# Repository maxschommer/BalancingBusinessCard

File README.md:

# business card

This is a persistence-of-vision (POV) business card, which is also NFC enabled
to aid in sharing contact information. POV is enabled by an accelerometer which
detects the end points of a swing of the card made by the user, and arranges
the letters to flash at the correct time in between two estimated end points
(the future end-point is guessed at by the length of the previous swing). Settings are changed by a capacitive sense button.

# Directory Structure

The firmare of the card is located in the `src` directory. The electrical
design files are in `design/business_card`. Images and other media are inside
`media`.

- [src](src/)
  - Contains the firmware of the card
- [design](design/)
  - Contains the KiCAD design files of the board
- [card_manufacturing](card_manufacturing/)
  - Contains python scripts used to generate GCODE to laser etch the aluminum top of the card.
- [media](media/)
  - Contains media (gifs, images, etc.)

# Building and Flashing Firmware

In order to flash the firmware, you must have the AVR toolchain installed.

`sudo apt-get install binutils gcc-avr avr-libc uisp avrdude flex byacc bison`

Then, navigate to the `src` directory and run `make` to build the object
file. In order to flash a business card, make sure to have your AVR programmer
plugged into your computer and connected to the board (and make sure the board
is appropriately powered!), then run

`make flash`

avrdude should say the the flash was successfull.

# Running manufacturing scripts

Some helper scripts exist to automate a lot of the manufacturing process for
customization. The scripts are specific to GRBL capable CNC machines (which
can laser etch). Scripts are written in python, and can be installed by
downloading the repository and running:

`pip install -e .`

Once the dependencies are installed, the scripts can be run from the root
directory, for example:

`python -m card_manufacturing.gcode_streamer`

## image_to_laser

This is a command line argument script which converts an image to an efficiently
rastered laser etcher GCODE path. It makes sure to utilize [laser mode](https://github.com/gnea/grbl/wiki/Grbl-v1.1-Laser-Mode) which
has been implemented in GRBL v1.1. The image is thresholded and the laser path
is binary (since the etching is all or nothing on coated aluminum). To get the
help for the script run:

`python -m card_manufacturing.image_to_laser -h`

## laser_calibration

This script generates a GCODE path to calibrate a CNC (with Z travel) with a
laser attachment. It progressively creates lines at different Z levels and
marks what the Z difference was on the line, so the user can identify the line
with the best marking and apply the appropriate offset for future etches. To
get the help for the script run:

`python -m card_manufacturing.laser_calibration -h`

## gcode_streamer

Finally, once GCODE is generated, the following script will stream the GCODE
to the CNC to run the part. To get the help for the script run:

`python -m card_manufacturing.gcode_streamer -h`

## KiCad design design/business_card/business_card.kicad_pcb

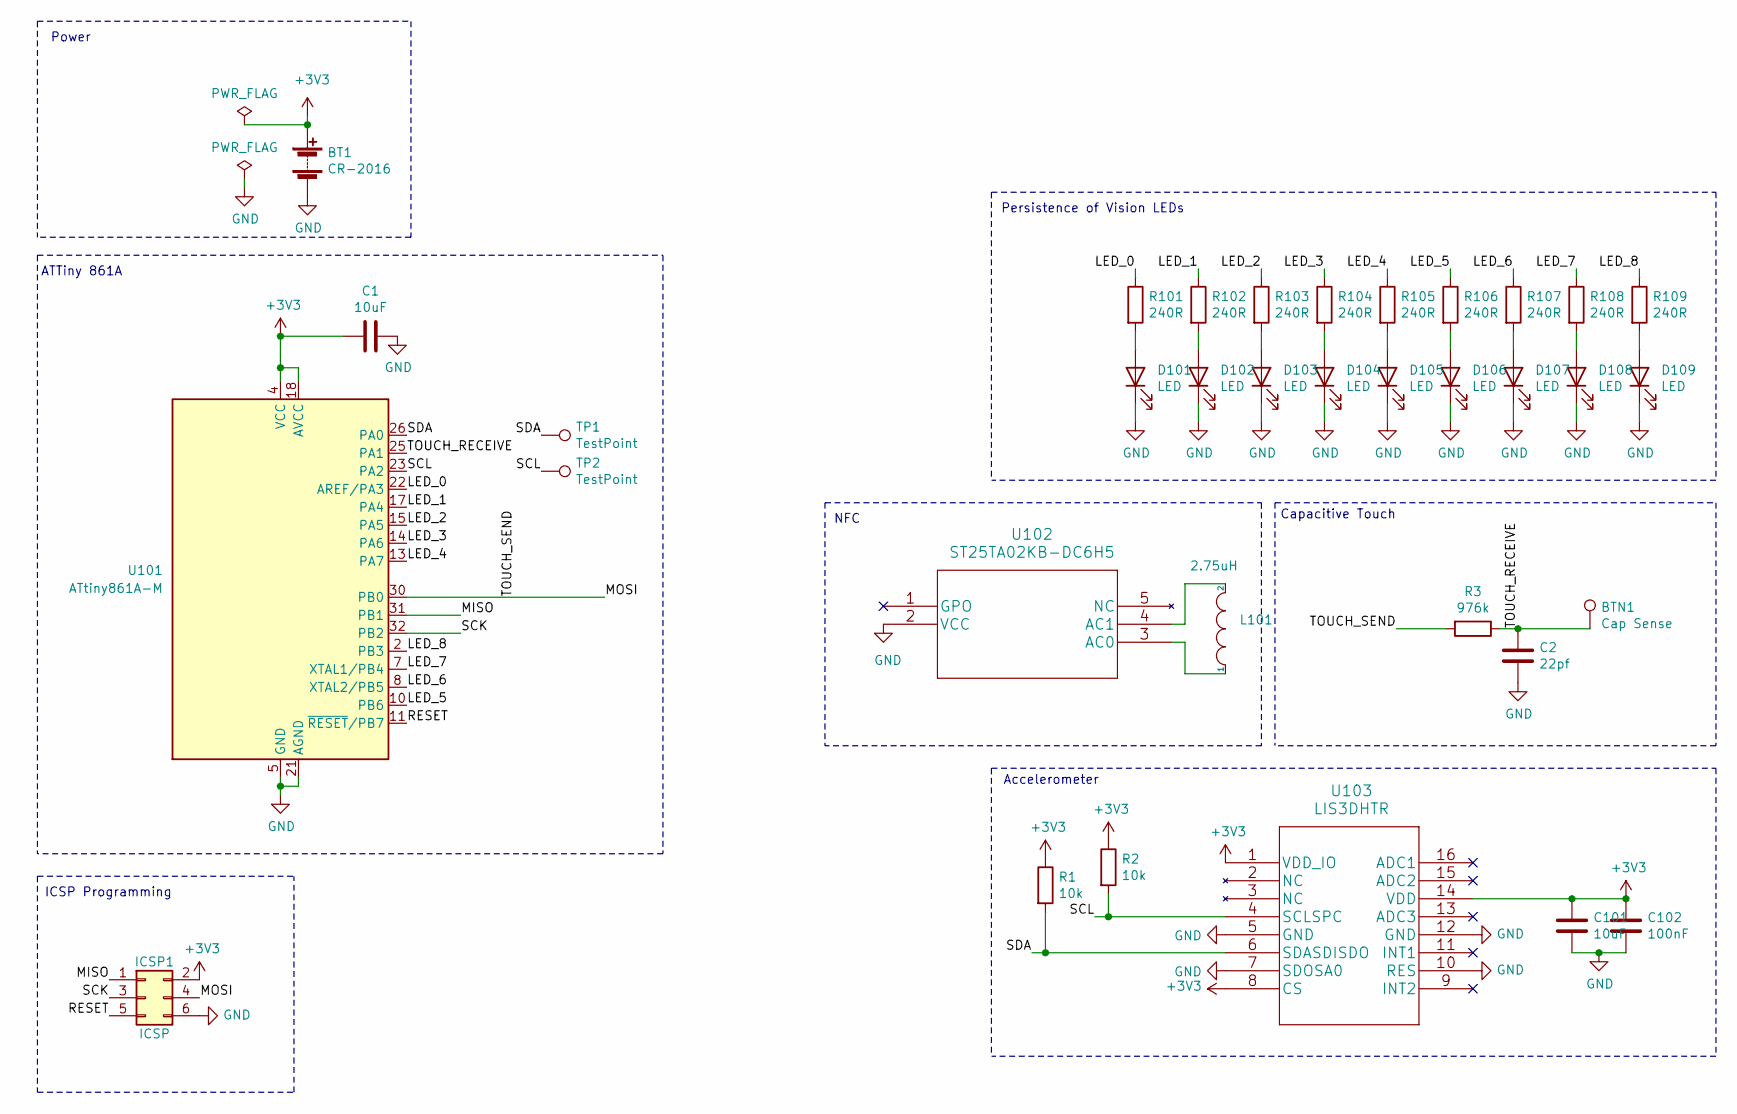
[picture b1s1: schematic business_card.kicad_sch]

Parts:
BT1: CR-2016; CR2016VP
BTN1: Cap Sense; CAP_TOUCH
C1, C101: 10uF; C_0805_2012Metric; Digikey 1276-6456-1-ND
C2: 22pf; C_0603_1608Metric; Digikey 732-7762-1-ND
C102: 100nF; C_0603_1608Metric; Digikey 311-1779-1-ND
D101, D102, D103, D104, D105, D106, D107, D108, D109: LED; LED_0603_1608Metric; Digikey 160-1183-1-ND
ICSP1: ICSP; PinHeader_2x03_P2.54mm_Vertical
L101: 2.75uH; Trace_Inductor_2_75uH
R1, R2: 10k; R_0603_1608Metric; Digikey 311-10KGRCT-ND
R3: 976k; R_0603_1608Metric; Digikey 311-976KHRCT-ND
R101, R102, R103, R104, R105, R106, R107, R108, R109: 240R; R_0603_1608Metric; Digikey 311-240GRCT-ND
TP1, TP2: TestPoint; TestPoint_Pad_D1.0mm
U101: ATtiny861A-M; QFN-32-1EP_5x5mm_P0.5mm_EP3.1x3.1mm; Digikey ATTINY861-15MZCT-ND
U102: ST25TA02KB-DC6H5; Digikey 497-19639-1-ND
U103: LIS3DHTR; Digikey 497-10613-1-ND

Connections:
+3V3: BT1.1 (+), C1.1, C101.1, C102.1, ICSP1.2, R1.1, R2.1, U101.4 (VCC), U101.18 (AVCC), U103.1 (VDD_IO), U103.8 (CS), U103.14 (VDD)
/LED_0: R101.1, U101.22 (AREF/PA3)
/LED_1: R102.1, U101.17 (PA4)
/LED_2: R103.1, U101.15 (PA5)
/LED_3: R104.1, U101.14 (PA6)
/LED_4: R105.1, U101.13 (PA7)
/LED_5: R106.1, U101.10 (PB6)
/LED_6: R107.1, U101.8 (XTAL2/PB5)
/LED_7: R108.1, U101.7 (XTAL1/PB4)
/LED_8: R109.1, U101.2 (PB3)
/MISO: ICSP1.1, U101.31 (PB1)
/MOSI: ICSP1.4, R3.2, U101.30 (PB0)
/RESET: ICSP1.5, U101.11 (~RESET~/PB7)
/SCK: ICSP1.3, U101.32 (PB2)
/SCL: R2.2, TP2.1, U101.23 (PA2), U103.4 (SCLSPC)
/SDA: R1.2, TP1.1, U101.26 (PA0), U103.6 (SDASDISDO)
/TOUCH_RECEIVE: BTN1.1, C2.1, R3.1, U101.25 (PA1)
GND: BT1.2 (-), C1.2, C2.2, C101.2, C102.2, D101.1 (K), D102.1 (K), D103.1 (K), D104.1 (K), D105.1 (K), D106.1 (K), D107.1 (K), D108.1 (K), D109.1 (K), ICSP1.6, U101.5 (GND), U101.21 (AGND), U101.33 (GND), U102.2 (VCC), U103.5 (GND), U103.7 (SDOSA0), U103.10 (RES), U103.12 (GND)
unnamed: D101.2 (A), R101.2
unnamed: D102.2 (A), R102.2
unnamed: D103.2 (A), R103.2
unnamed: D104.2 (A), R104.2
unnamed: D105.2 (A), R105.2
unnamed: D106.2 (A), R106.2
unnamed: D107.2 (A), R107.2
unnamed: D108.2 (A), R108.2
unnamed: D109.2 (A), R109.2
unnamed: L101.1, U102.3 (AC0)
unnamed: L101.2, U102.4 (AC1)

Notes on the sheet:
Power
ATTiny 861A
ICSP Programming
NFC
Accelerometer
Persistence of Vision LEDs
Capacitive Touch

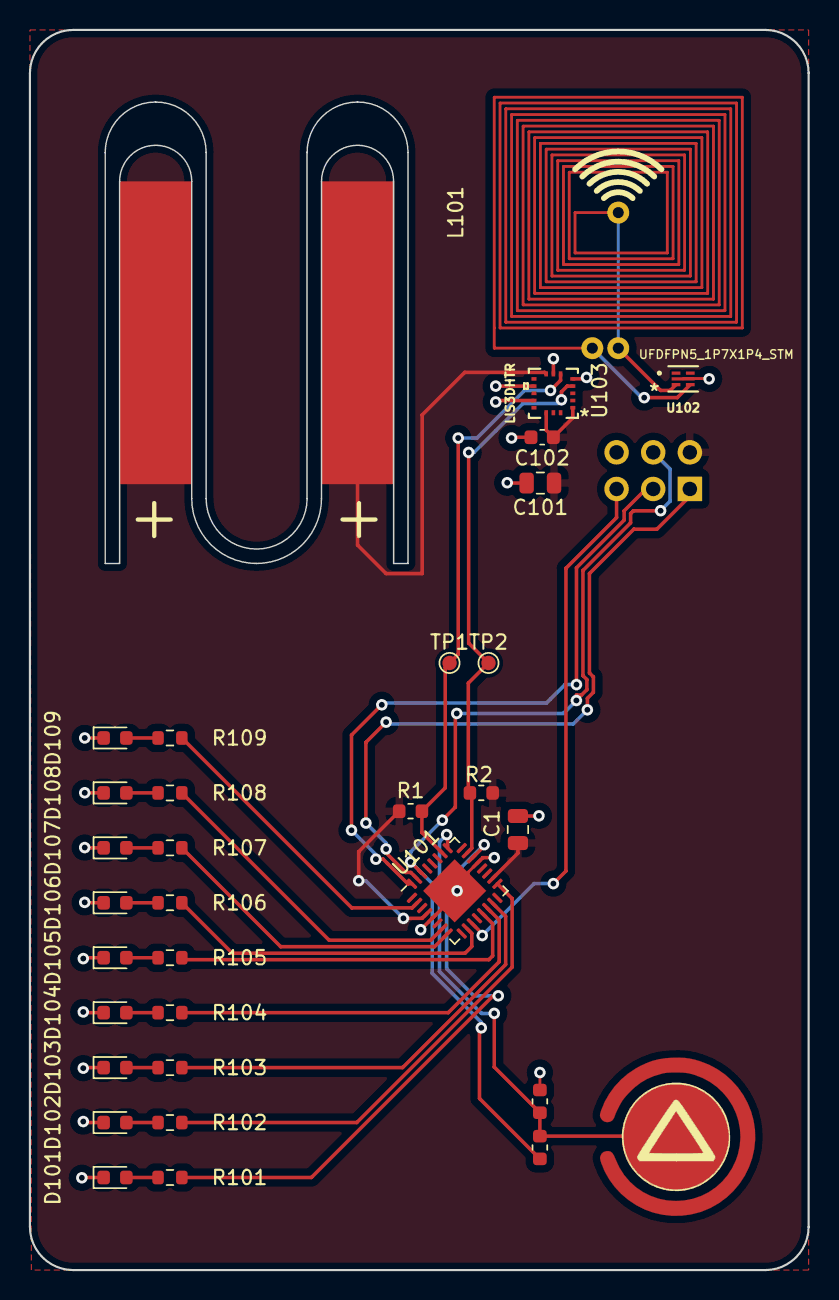
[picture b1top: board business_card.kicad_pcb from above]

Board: 2 copper layers, 54.0 x 86.0 mm, 34 parts (1 on the bottom side), 29 nets.

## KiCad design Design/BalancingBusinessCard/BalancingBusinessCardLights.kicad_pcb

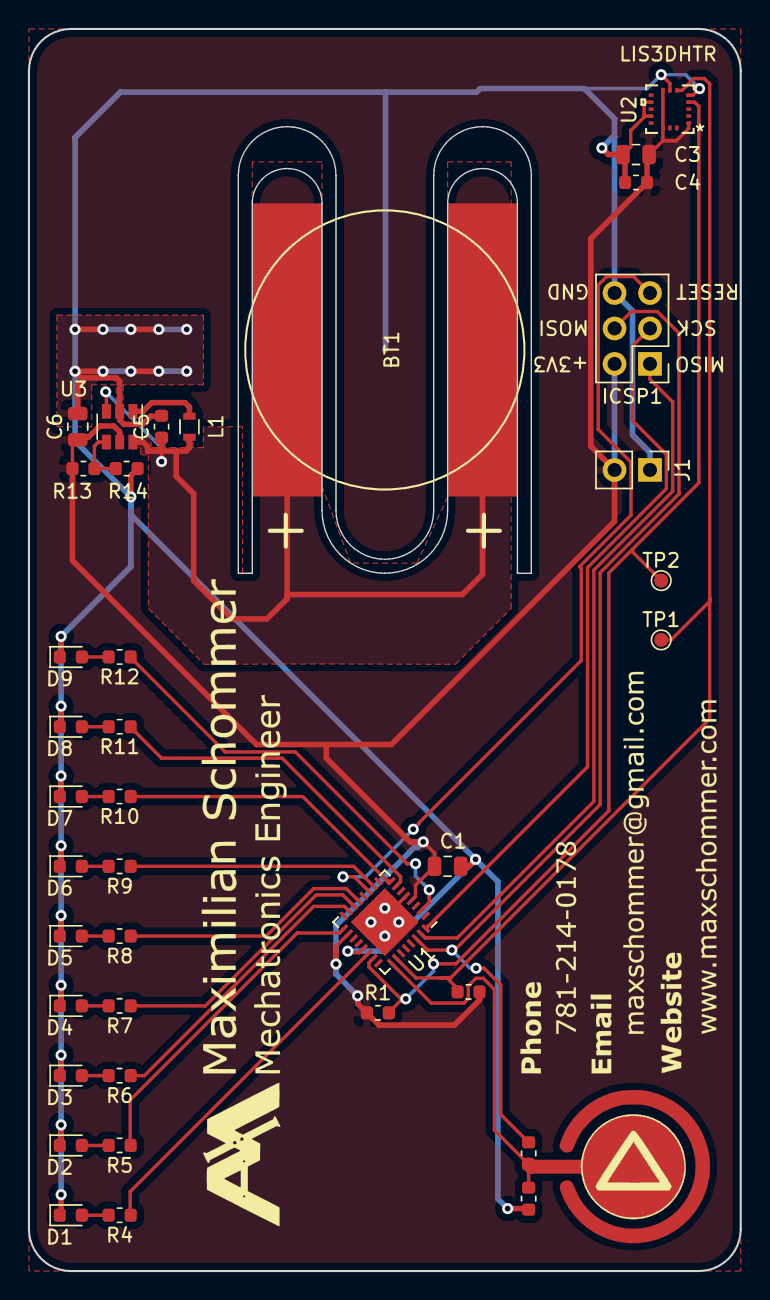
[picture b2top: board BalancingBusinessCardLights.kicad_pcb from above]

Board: 2 copper layers, 51.0 x 89.0 mm, 39 parts (0 on the bottom side), 30 nets.

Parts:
BT1: CR-2016; CR2016VP
BTN1: Cap Sense; CAP_TOUCH
C1, C3, C6: 10uF; C_0805_2012Metric
C2: 22pf; C_0603_1608Metric
C4: 100nF; C_0603_1608Metric
C5: 4.7uF; C_0603_1608Metric
D1, D2, D3, D4, D5, D6, D7, D8, D9: LED; LED_0603_1608Metric
ICSP1: ICSP; PinHeader_2x03_P2.54mm_Vertical
J1: PWR; PinHeader_1x02_P2.54mm_Vertical
L1: 4.7uH; L_0603
R1, R2: 10k; R_0603_1608Metric
R3, R13: 976k; R_0603_1608Metric
R4, R5, R6, R7, R8, R9, R10, R11, R12: 240R; R_0603_1608Metric
R14: 562k; R_0603_1608Metric
TP1, TP2: TestPoint; TestPoint_Pad_D1.0mm
U1: ATTINY861-15MZ; QFN-32-1EP_5x5mm_Pitch0.5mm
U2: LIS3DHTR
U3: MCP1640DT-I/CHY; SOT-23-6

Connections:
+3V3: C1.1, C3.1, C4.1, C6.1, ICSP1.2, J1.2, R1.1, R2.1, R13.1, U1.4, U1.18, U2.1, U2.8, U2.14, U3.5
+BATT: BT1.1, C5.1, L1.2, U3.3, U3.6
/LED_0: R4.1, U1.22
/LED_1: R5.1, U1.17
/LED_2: R6.1, U1.15
/LED_3: R7.1, U1.14
/LED_4: R8.1, U1.13
/LED_5: R9.1, U1.10
/LED_6: R10.1, U1.8
/LED_7: R11.1, U1.7
/LED_8: R12.1, U1.2
/MISO: ICSP1.1, U1.31
/MOSI: ICSP1.4, R3.2, U1.30
/RESET: ICSP1.5, U1.11
/SCK: ICSP1.3, U1.32
/SCL: R1.2, TP2.1, U1.23, U2.4
/SDA: R2.2, TP1.1, U1.26, U2.6
/TOUCH_RECEIVE: BTN1.1, C2.1, R3.1, U1.25
GND: BT1.2, C1.2, C2.2, C3.2, C4.2, C5.2, C6.2, D1.1, D2.1, D3.1, D4.1, D5.1, D6.1, D7.1, D8.1, D9.1, ICSP1.6, J1.1, R14.2, U1.5, U1.21, U1.33, U2.5, U2.7, U2.10, U2.12, U3.2
unnamed: D1.2, R4.2
unnamed: D2.2, R5.2
unnamed: D3.2, R6.2
unnamed: D4.2, R7.2
unnamed: D5.2, R8.2
unnamed: D6.2, R9.2
unnamed: D7.2, R10.2
unnamed: D8.2, R11.2
unnamed: D9.2, R12.2
unnamed: L1.1, U3.1
unnamed: R13.2, R14.1, U3.4

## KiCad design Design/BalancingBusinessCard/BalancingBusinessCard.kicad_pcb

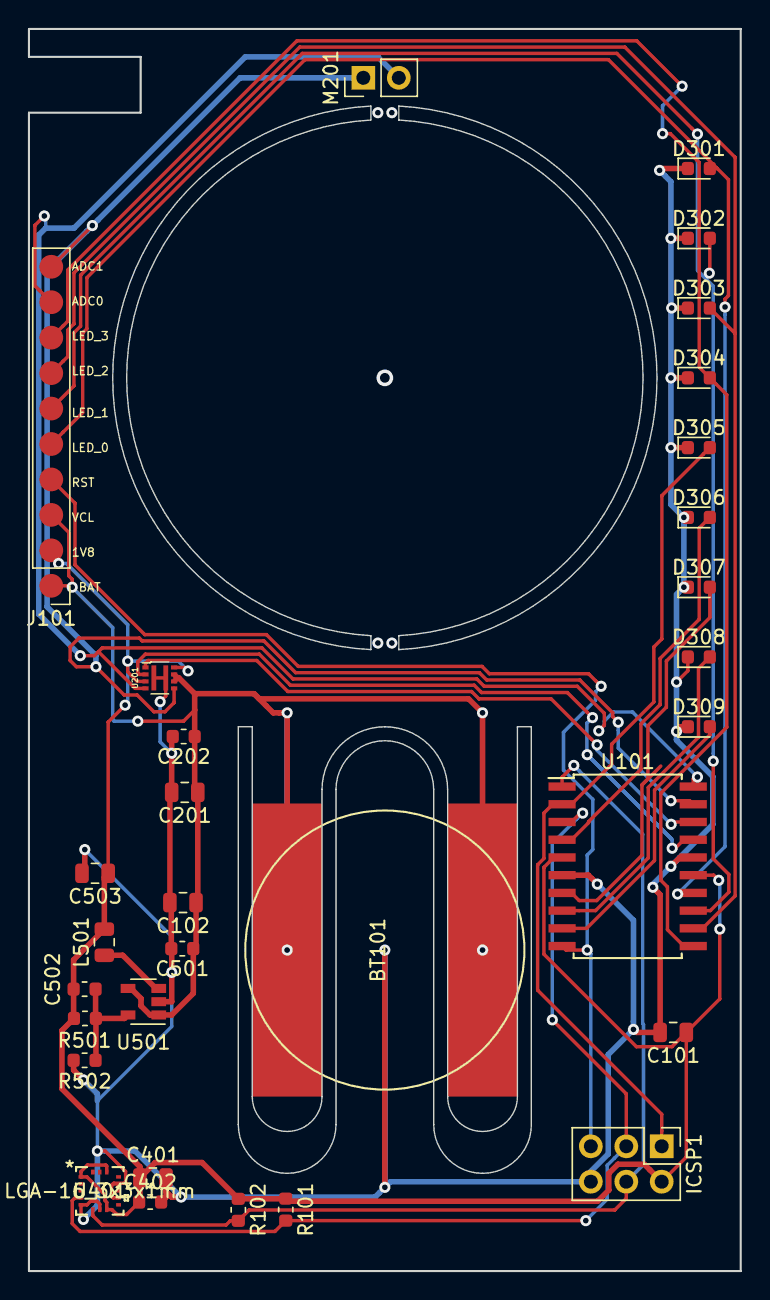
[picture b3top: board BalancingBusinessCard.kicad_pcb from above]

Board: 2 copper layers, 51.0 x 89.0 mm, 31 parts (0 on the bottom side), 21 nets.

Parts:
BT101: Battery; CR2016VP
C101, C102, C201, C401, C503: 10uF; C_0805_2012Metric
C202: 1uF; C_0603_1608Metric
C402: 100nF; C_0603_1608Metric
C501: 4.7uF; C_0603_1608Metric
C502: 22pF; C_0603_1608Metric
D301, D302, D303, D304, D305, D306, D307, D308, D309: LED; LED_0603_1608Metric
ICSP1: Conn_02x03_Odd_Even; PinHeader_2x03_P2.54mm_Vertical
J101: TestPoints; Testpoint_1x10
L501: 2.2uH; L_0805_2012Metric
M201: Motor_DC; PinHeader_1x02_P2.54mm_Vertical
R101, R102: 1k; R_0603_1608Metric
R501: 100k; R_0603_1608Metric
R502: 200k; R_0603_1608Metric
U101: ATtiny261-20SU; SOIC-20W_7.5x12.8mm_P1.27mm
U201: AP1017AEN
U401: LGA-16_3x3x1mm; LIS3DHTR
U501: FT440CA; SOT-23-5

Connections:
+1V8: C101.1, C401.1, C402.1, C502.1, C503.1, ICSP1.2, J101.2, L501.2, R101.1, R102.1, R502.2, U101.5, U101.15, U201.3, U201.8, U401.1, U401.8, U401.14
+BATT: BT101.1, C102.1, C201.1, C202.1, C501.1, J101.1, J101.3, U201.6, U201.7, U501.1, U501.4
/ADC0: J101.9, M201.2, U101.20, U201.4
/ADC1: J101.10, M201.1, U101.19, U201.5
/INA: U101.18, U201.1
/INB: U101.17, U201.2
/LED_0: D301.2, J101.5, U101.14
/LED_1: D302.2, J101.6, U101.13
/LED_2: D303.2, J101.7, U101.12
/LED_3: D304.2, J101.8, U101.11
/LED_4: D305.2, ICSP1.1, U101.2
/LED_5: D306.2, U101.4
/LED_6: D307.2, U101.7
/LED_7: D308.2, U101.8
/LED_8: D309.2, U101.9
/MOSI: ICSP1.4, R102.2, U101.1, U401.6
/RESET: ICSP1.5, J101.4, U101.10
/SCK: ICSP1.3, R101.2, U101.3, U401.4
GND: BT101.2, C101.2, C102.2, C201.2, C202.2, C401.2, C402.2, C501.2, C503.2, D301.1, D302.1, D303.1, D304.1, D305.1, D306.1, D307.1, D308.1, D309.1, ICSP1.6, R501.1, U101.6, U101.16, U201.9, U401.5, U401.7, U401.10, U401.12, U501.2
unnamed: C502.2, R501.2, R502.1, U501.5
unnamed: L501.1, U501.3

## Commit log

2018-10-20 Made a business card simulator including sensors
2018-10-21 Made module sheets
2018-10-21 Made a part
2018-10-21 Fixed reference
2018-10-21 pulling ref change
2018-10-21 Made more parts
2018-10-21 Added ICSP header
2018-10-21 makin more footprints!
2018-10-21 Making filter
2018-10-21 Added IMU
2018-10-21 Ignored cache and backup files
2018-10-21 More LC filter
2018-10-21 Wired up LEDs
2018-10-21 scrapped an inductor filter
2018-10-21 Added power electronics for main chip
2018-10-21 Fixed stuff
2018-10-21 Assigned numbers
2018-10-21 Footprint assignment
2018-10-21 Added regulator
2018-10-21 Made battery footprint
2018-10-21 Got Schematic CRC running
2018-10-21 Final schematic assignments
2018-10-21 Layout started
2018-10-21 Layin out
2018-10-21 Layout
2018-10-21 Made battery and circle centered and added edge cuts
2018-10-21 Moved stuff
2018-10-21 Routed IMU and Regulator
2018-10-21 messiest of merges
2018-10-21 More routing on motor driver
2018-10-21 Finished MCU
2018-10-21 Wired ground
2018-10-21 Work on pads
2018-10-21 Manual cleanup
2018-10-21 Automatic cleanup
2018-10-21 Did text
2018-10-21 Fixed routing
2018-10-21 Passed DRC
2018-10-21 Added ground pour
2018-10-21 added text
2018-10-21 Added .kicad_pcb-bak to gitignore
2018-10-21 Final from Saturday
2018-10-21 Made mousebites and improved battery tab
2018-11-12 Programming starting
2018-11-12 BOM stuff
2018-11-12 Blinky
2018-11-12 Everything blinks, the Makefile is still garbage
2018-11-12 Fixed Makefile
2018-11-12 Started real code
2018-11-12 Made a dodaloop
2018-11-12 Added replay code
2018-11-12 Working zigzag
2018-11-12 Hello World
2018-11-12 Working motor
2018-11-12 Lights + Motor
2018-12-07 Moded power schematic for fixed version
2018-12-10 Completed Lights board schematic
2018-12-10 Finished light board layout and silkscreen design
2018-12-11 Made Eric logo
2018-12-14 Rev2 Shipped
2019-01-09 Made working tilt switch code
2019-01-12 broken, getting i2c to work
2019-01-26 Working code
2019-01-26 Make makefile work
2019-01-26 Working i2c address sending
2019-02-20 Work
2019-02-20 Working data reading
2019-02-20 Working 9-bit display
2019-02-20 Nevermind, LEDs dont work
2019-02-20 Revert "Working 9-bit display"
    This reverts commit 6f789adadc6e6a2334bb884a12fdf926cae32f34.
    # Conflicts:
    # src/main.cpp
2019-02-20 Working IMU read
2019-02-20 Working and compiling lis3dh library, doesn't fit in space...
2019-02-20 Removed unneeded libraries
2019-02-20 Refactored accelerometer utils to separate file
2019-02-20 Actually working 9-LED display
2019-02-20 Working accelerometer reading
2019-02-20 Clock speeds fixed
2019-02-20 Faster I2C
2019-02-20 Added Analog Discovery workspace
2019-03-04 Edge detectors and stuff
2019-03-04 Working edge detection
2019-03-04 16g mode
2019-03-04 Working image display with return stroke!
2019-03-04 Refactored to be synchronous
2019-03-04 Working dual-period scheme
2019-03-04 Dual periods
2019-03-04 Working replay stuff
2019-03-05 Minor work on code stuff
2019-03-05 Began v3 board design
2019-03-05 Basic layout for v3
2019-03-05 Final changes from the night
2019-03-09 Added explicit routing for most ground and power wires
2019-03-09 Moved all components to top half of board
2019-03-12 Added some images
2019-03-12 Updated ground pour to avoid thermal relief
2019-03-12 Minor board tweaks
2019-03-12 Reverted layout to old one for text placement
2019-03-12 Added new components
2019-03-12 Right Stuff
2019-03-12 Made touch sense cap
2019-03-12 Fixed .gitignore
2019-03-12 Fixing stuff
2019-03-12 Made custom test point symbol
2019-03-12 Got a better test point
2019-03-12 Updated orientation of button
2019-03-12 Cleaned up fills
2019-03-16 Various SVG files
2019-03-31 Minor DRC fixes
2019-03-31 Updated BOM
2019-03-31 Updated names
2019-03-31 Updated resistor values
2019-04-30 Fixed one-character typo
2019-04-30 Progress
2019-04-30 Made ADC work
2019-04-30 Working touch send
2019-04-30 Working ADC timing
2019-04-30 Working digital read cap sensing
2019-04-30 Counter
2019-04-30 Typo fix
2019-04-30 Memory leaks :(
2019-04-30 Moved alphabet out of RAM
2021-02-08 Cleaned repo and reorganized business card for new dimensions and NFC
2021-02-08 Deleted remaining files
2021-02-08 Deleted more spurious files
2021-02-08 Deleted more spurious files and fixed design so it builds properly
2021-02-11 Routing complete
2021-04-18 Deleted kicad session file, tested image_to_laser
2021-07-09 Removed commented code
2021-07-12 Improved laser and gcode streamer components
2021-07-12 Added gcode streamer
2021-07-12 Added laser calibration routine
2021-07-21 Reformatted annotations, refactored gcode_streamer
2021-07-21 Improved documentation
2021-07-27 Preparing version 4 for manufacture

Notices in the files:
parts and their libraries:
Copyright 2016 Accelerated Designs. All rights reserved.
